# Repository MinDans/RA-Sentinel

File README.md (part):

# Project RA-Sentinel - a Radio Access Sentinel
FPGA-based Radio Receiver for securing Wifi an other access points against hacking attacks.

RA-Sentinel is an open-source project focused on creating a cost-effective, small, and low-power wide band radio receiver device that employs an FPGA to automatically detect malicious attacks on Wifi access points, such as Man in the Middle and Denial of Service attacks. By monitoring any Wifi cell, the device enhances internet safety for everyday users.
The device features low-cost receive-only chips that digitize 40 MHz of the Wifi radio spectrum at 2.4 GHz. An FPGA extracts relevant properties from demodulated and decoded packets in real-time without storage. These properties are then processed by a neural network, also implemented on the FPGA, to determine if the traffic is genuine or an attack.

 <br>
This project was funded through the NGI0 Entrust Fund, a fund established by NLnet with financial support from the European Commission's Next Generation Internet programme, under the aegis of DG Communications Networks, Content and Technology under grant agreement No 101069594.

## Latest Updates [15. Dec. 2025]

Added new firmware für the STM32 microcontroller ECU (Embedded Control Unit) on the Backend Board in "/RASBB/Software/RASBB_ECU".
It adds support for UPNP device discovery over Ethernet and provides a system configuration web page.

## System architecture

## The hardware

The hardware is a wide band SDR receiver that receives at least one complete WiFi Channel on the 2.4GHz ISM band with high resolution (12 Bits) to be able to detect smallest anomalies in a transmitted signal. The initial evaluation hardware consists of a Downcoverter/Tranceiver Chip for 2.4GHz which is widelay used in older WIFi Acess Points (MAX2831). This is followed by a 12 Bit ADC (Texas Instruments ADC3222) which converts a 40MHz window of the 2.4GHZ radio spectrum into a 4 x 240 Bit/s LVDS streams (960kBit/s total) into a XILNIX/AMD Artix7 FPGA sitting on a evaluation board made by QMTECH. 

<sub>Picture 1: First RA-Sentinel prototype based on the QM-Tech Artix7 board and a new designed RF front end connected via PMOD connector.</sub>

Based on the experience collected with with first prototype, we designed a new SDR prototypr. Two boards of the RASBB and the RASRF2400 have arrived on 23th. Feb. 2025
Testing and bringing up is now ongoing. First results and findings can be found in the corresponding Findings_Rev*.md documents.

<sub>Picture 2: RA-Sentinel prototype Revision A with RF front end board RASRF2400WB.</sub>

### Design files

**/RFFE2400WB** in this folder of this repository you find the PCB design files in KiCAD format and gerbers for the 2.4GHz 2x PMOD connected RF frontend evaluation/test board.

Link to the FPGA dev. board
[https://de.aliexpress.com/item/1005006473783593.html]

## Software / Firmware

The vast majority of the code will be written in Verilog and run on the FPGA. There is also now a firmware for the RASBB_ECU (Embedded Control Unit) and a"house keeping unit" microcontroller (STM32C031) which programms and controlling the frontend chips. The RASBB_ECI provides the interconnctivity with other systems (alarm forwarding) and the web configuration interface. This firmware is written in C. 

The firmware for the RASBB_ECU can be found <a href="https://github.com/Tobias-DG3YEV/RA-Sentinel/tree/main/RASBB/Software/RASBB_ECU">here</a>. 

The RASBB_ECU Firmware for the onboard STM32 provides a versatile configuration interface with GUI that allows to show statistics and maybe UDP for analytic packets transfer and secure TCP/IP configuration over Ethernet.
To access this, enter the IP of the RAS into your local browser like http://192.168.0.2:4842/. The IP can be easily found via network environment because the RAS supports UPNP over ethernet.

A suspected WiFi node can be

* Tracked: Monitored by relative signal strength and later with additional direction. These values are forwarded to an IDS host that can combine this information with additional data retrieved from different RAS or other network monitoring systems.
* Tagged: Marked for internal memory, moving up in watch list.
* Fingerprinted: Raw IQ data of the frame start is forwarded to a fingerprinting algorythm.

**UPNP support**

To ease the installation process, the RAS can be connected to any ethernet based LAN that provides an IPv4 DHCP server. Through the UPNP support, the RAS is easy to find in any network browser of Windows, Linux and Mac etc. 

---
## Sub project: RASRF2400WBMC - Directional RF Front End

The **RASRF2400WBMC** is a 4-channel, phase-coherent 2.4 GHz RF front-end board that extends RA-Sentinel with **Angle of Arrival (AoA)** estimation. By receiving the same signal across four spatially separated antennas, the system can estimate the physical direction of a detected attack - enabling threat localization for jamming, spoofing and unauthorized events.

This board connects to the existing RASBB via the PCIe connector and requires no hardware changes to the base band board.

> This sub-project was funded by NLnet: https://nlnet.nl/project/RA-Sentinel-directional/

See [RASRF2400WBMC/README.md](RASRF2400WBMC/README.md) for full details.

---

### Sub Projects / Project steps

The first step on this project was to have a reliable hardware basis. Initially I planned to have at least 40 Megasamples and with this 20 MHz bandwidth which is sufficient to capture the headers and the most common bandwitdhs used on 2.4GHz WiFi (802.11a,b,g) communications channel. But because 802.11n also defines the possibility to use 40MHz bandwith, I wanted the possibility to cover the complete possible channel bandwidth. This has been achieved with the first prototype hardware and prooved with the sub-project RASM2400, Radio Access Spectrum Monitor for 2400MHz. You can find all project details below.

## Sub project #1: RASM2400 - a spectrum monitor

RASM2400 stands for Radio Access Spectrum Monitor operationg on 2400MHZ. It offers a visual spectrum analyzer design that runs on the evaluation hardware set of RA-Sentinel the Artix7 XC7A100T Wukong board and the RFFE2400 front end board.
It shall proove that a 40MHz wide radio spectrum can be received and transported into the FPGA. Further, this project may already be useable for first RF forensics. Feel free to download all the stuff and build an RASM by yourself.

The following diagram shows the system architecture of the RASM2400.

The output of the HDMI port of the QMTECH Wukong board.

Watch a short demonstration on Youtube by clicking on the thumbnail below.

### Software

In this repository you'll find also all software paerts needed to get the project up and running.

**/RASM2400_Verilog**

This folder contains the Verilog source files as well as a ready to program bit stream file. 

**/RASM2400_HKU**

Here you find the firmware for the RF board housekeeping unit. It does not do much a the moment but initializing the Downconverter MAX2831 and the ADC3222. It is planned to receive commands via I2C to change basic parameters wil center frequency, sensitivity and AGC characteristics. This porject can be compiled with arm-gcc or with the free available and Eclipse based development environment (IDE) from ST called "STM32CubeIDE". You can download this IDE from ST.com [https://www.st.com/en/development-tools/stm32cubeide.html]

### Project update 13th Oct. 2024

The target of the next Milestone #2 was the „Identification and isolation of appropriate software components“ and also to „Additionally apply modifications to the openOFDM module to get extra meta data out of the frame demodulator to have a wider data basis for the later fingerprinting process.“

In the following points I describe how I achieved each step of this Milestone.

**1. compile/synthesize openWiFi on the target FPGA**

The code of openWiFi has been successfully ported from the project GitHub site [1] to the evaluation setup that I have designed and set up in the first Milestone. After gluing together the ADC LVDS deserializer block inside the FPGA with the parallel input of the openOFDM core, got rid of several timing constraint issues, I finally achieved to decode a WiFi Frame coming from an arbitrary signal generator. To accomplish this target, the code needed to be isolated from the original open WiFi demo project code. This original demo was based on SDR evaluation boards relying all on the AMD ZYNQ FPGA-ARM chip family. This family provides an FPGA part and an integrated ARM micro processor to which all communication of the FPGA part is connected to. Data from and to the integrated processor is exchanged through a common memory bus. This however is not working with my design idea which is based on a more powerful FPGA with an external ARM co-processor. I tried extracting the needed HDL (Verilog) parts and make this code running stand-alone. Finally I came the conclusion that only the project „openOFDM“ needs to be ported to my RA-Sentinel project hardware because the network layer and the transmit part implemented in openWiFi is not really needed by the RA-Sentinel project because there is no need in routing real data back and forth to a network. We are only interested in the lowest layer of a WiFi frame and its analog characteristics, not the routing of packets and also not in the frame containing payload as such.

First I adapted the test-bench provided in [2] for the Vivado simulation environment. To be able to simulate the complete RA-Sentinel hardware, I created a LVDS emulator that can stream artificial synthesized and recorded  RF data coming originally from the TI ADC 3221. After providing recorded RF data via this LVDS simulator and generating a appropriate, to the ADC phase-locked master clock of 100MHz to the openOFDM core and (see top_tb.v), this setup was able to decode a complete 802.11a/g frame in the AMD Vivado simulator. It took me quite some fiddling and playing with timings and implementation settings of the tool-chain to finally get it running properly on my own hardware. (AMD Artix7 development board my QM-Tech and my 2.4GHz ADC board designed in Milestone 1)

**2. Strip down openWiFi and open OFDM to the receive part**

First this was regarded as an easy task but as deeper I dived into the code  by the original author of the two projects, the more I realized the code provides almost no comments and wire and register definitions are quite ambiguous and non-intuitive. In my opinion the code needed desperately a rework to be better understandable which would also lead to a lower learning curve for others also trying to implement and adapt the existing code base to their needs. Two major things I tried improving with my fork of openOFDM: The introduction of directional prefixes for module ports. I have seen such in the code of another NLnet founded guy called Dan Nissselquist. Adding the prefix  „i_“ to  input ports (defined as wires/registers in Verilog) and „o_“ to the port definition makes it IMHO much easier when browsing through the code, allowing to instantly realize which wire or register is being exported from this current module and which is only a local element. I added these prefixes all over the code of openOFDM. See my fork of openOFDM on GitHub [1] for details. The next thing I found hard to understand, was the use of the ever repeating word „sample“ for all data along the signal path, from the input of the openOFDM core (ADC base-band data) up to near the exit (decoded data bytes). As there is a switch from time domain (endless sample stream) into frequency domain (blocks of 64 frequency bands) in the module „sync_long“, I changed the name of all wires and registers after this module and renamed them into „spectrum“.  Also some comments were added to clarify what a wire or register is doing at a certain point. This work is not yet regarded as being completed. Each time I dig into the original code, I will add comments and try to make the code more „barrier free“.

**3. Create a new fork of openOFDM**

This has been done and the new fork of openOFDm can be found here:

[1] https://github.com/Tobias-DG3YEV/openofdm

It contains comments and my code changes proposed earlier in this document.

**4. Try adding additional meta date stubs**

As I tried figuring out which meta data could be used to distinguish between  genuine transmitting device and a counterfeit device, I found an article at mathworks.com [3] reporting that they proved finding counterfeit, evil twins of a WiFi Access Point by feeding the raw sampled channel data of a transmission into a ML algorithm. For this purpose they followed a kind of a brute force approach by taking all samples of a received frame into account and fed into a ML algorithm. Even the smallest frame like an information or flow control frame that is only 100uS of duration will produce 16kBytes of data which is rather huge. This amount of data may be processable - if the SDR is directly connected to a powerful computer with multiple cores etc. The project RA-Sentinel does not follow this kind of big processing power approach. Amplitude, phase and frequency change due to several effects during the transmission of a frame, but all of these changes always result in a phase shift. So I thought, in  the first attempt identifying a WiFi transmitting device by characterizing (or say learning) the phase deviation over time may be sufficient. Because the RF receiver front end of the RA-Sentinel project has a low noise and high stability master clock (a 40MHz TXCO by Abracom) that is multiple times more accurate that standard commercial WiFi transmitters, I hope that a small amount of phase shift data received in the beginning of a WiFi frame may be enough to clearly identify counterfeit devices. 

**5. Redefine a new simplified interface to access meta parameters**

One thing I have learned throughout the project progress so far, is that even many may say that an FPGA is one of the most versatile digital programmable devices available today, allowing the implementation of any kind of parallel and sequential tasks up to integration of soft-core processors the fact is that all this integrated logic leads to a rather time consuming iterative development process. To optimize WiFi data reception on one side and to interpret and forward meta data on the other side all inside the FPGA leads to an extremely slow and challenging development process. For the analysis of meta data, an external, traditional single chip microprocessor running straight C/C++ code,  offers much more opportunities and most importantly, allows much a faster  development progress. Bit for that, I need a fast and reliable interconnection between the FPGA and the micro processor.

I identified and implemented two interfaces which allow to access 

The first interface I implemented into the FPGA was the SPI slave interface. This interface allows reading and writing 32 wide registers inside the FPGA by an external micro controller (in this case, I use a STM32H743 Cortex-M7)

The SPI interface allows access to the following parameters:

- Receiver characteristics like receiver center frequency, gain, power threshold, max. error rate etc.

- reading current receiver parameters like noise level, signal to noise ratio etc.

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
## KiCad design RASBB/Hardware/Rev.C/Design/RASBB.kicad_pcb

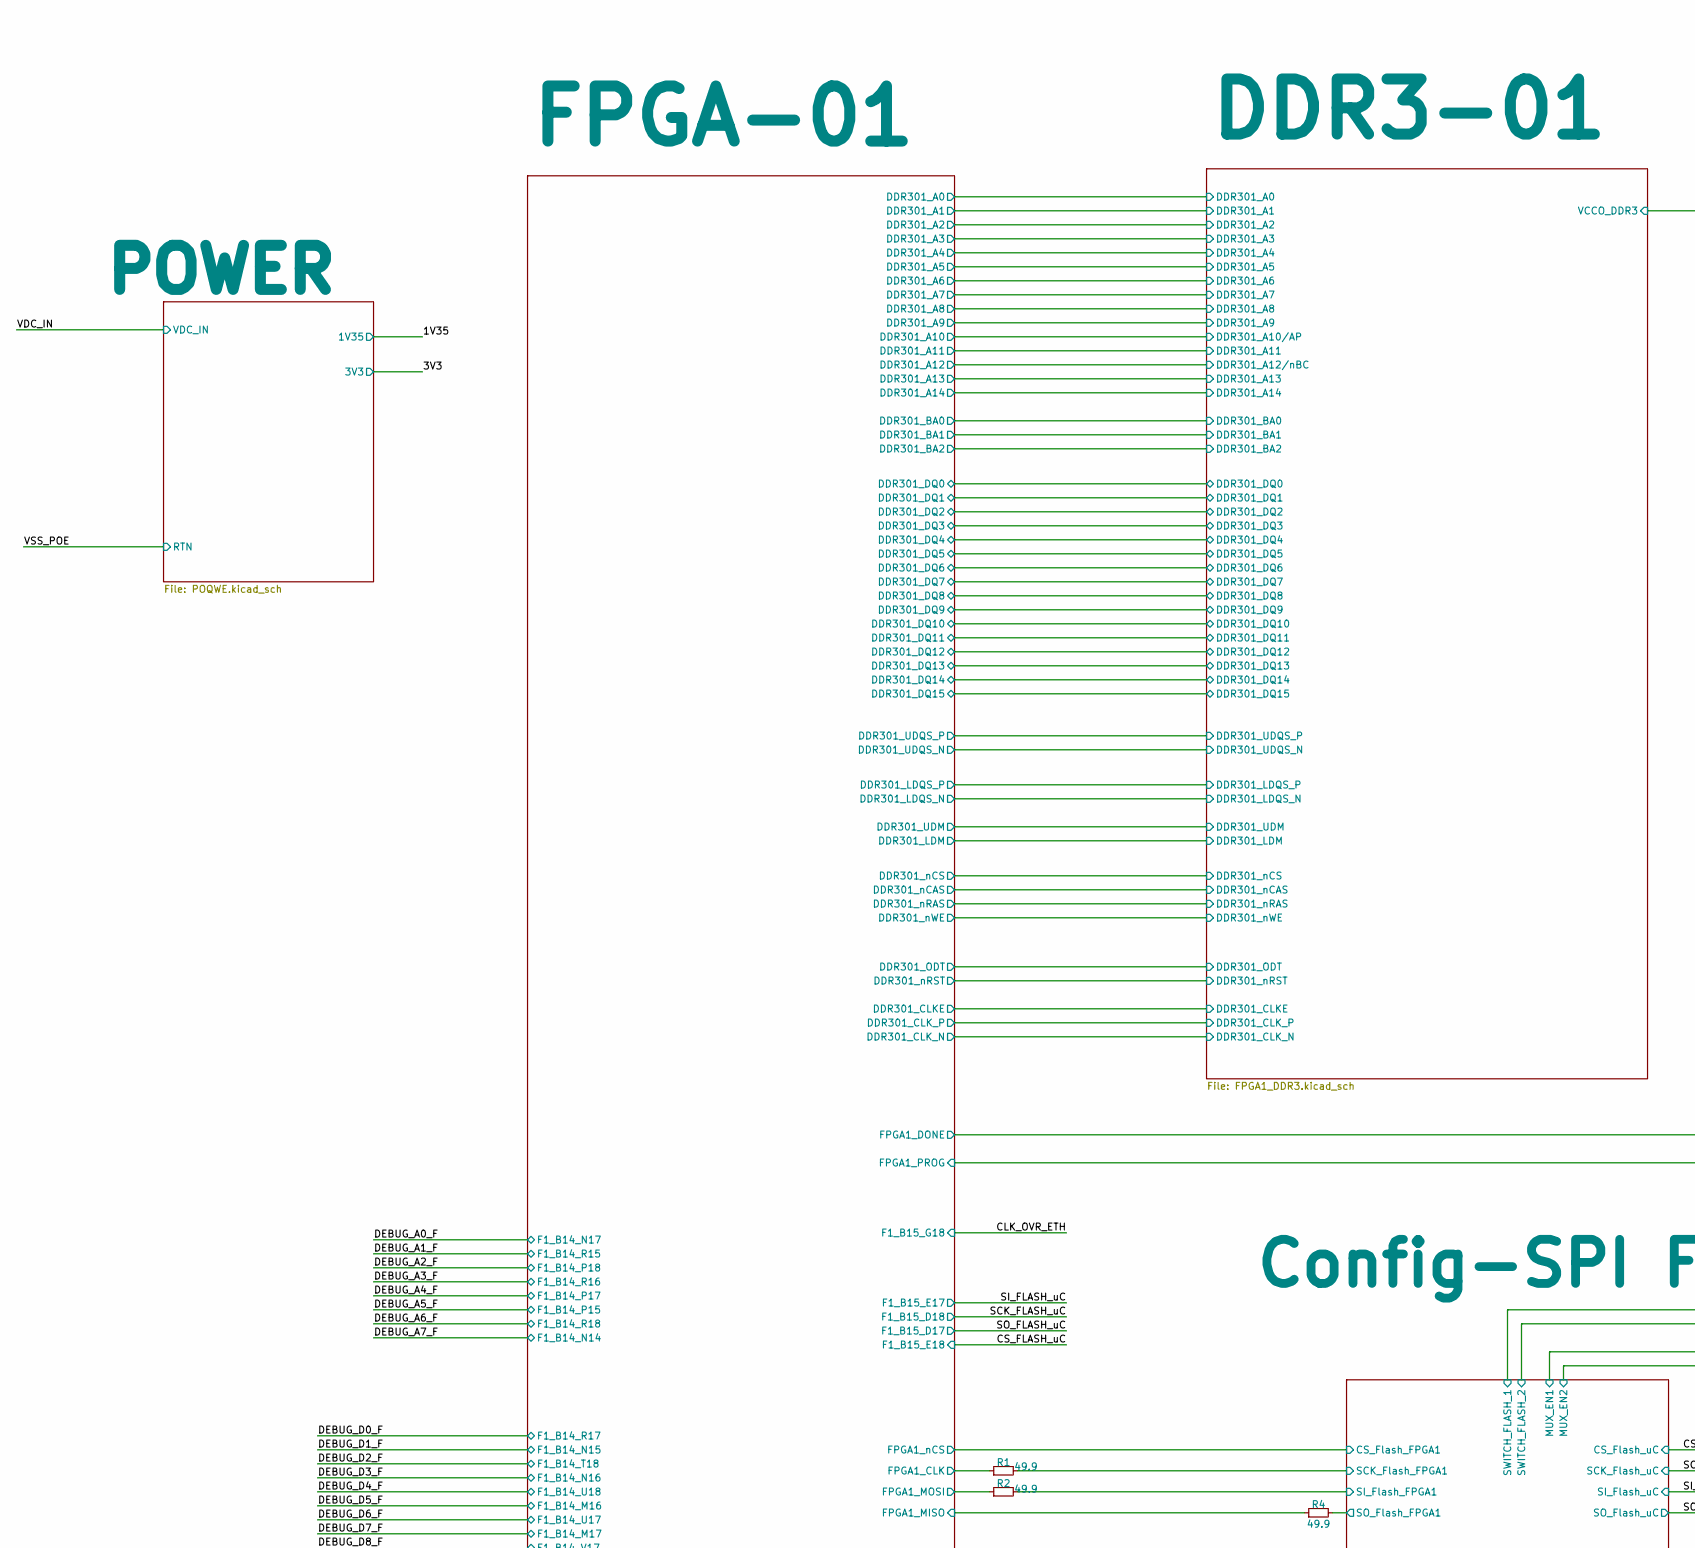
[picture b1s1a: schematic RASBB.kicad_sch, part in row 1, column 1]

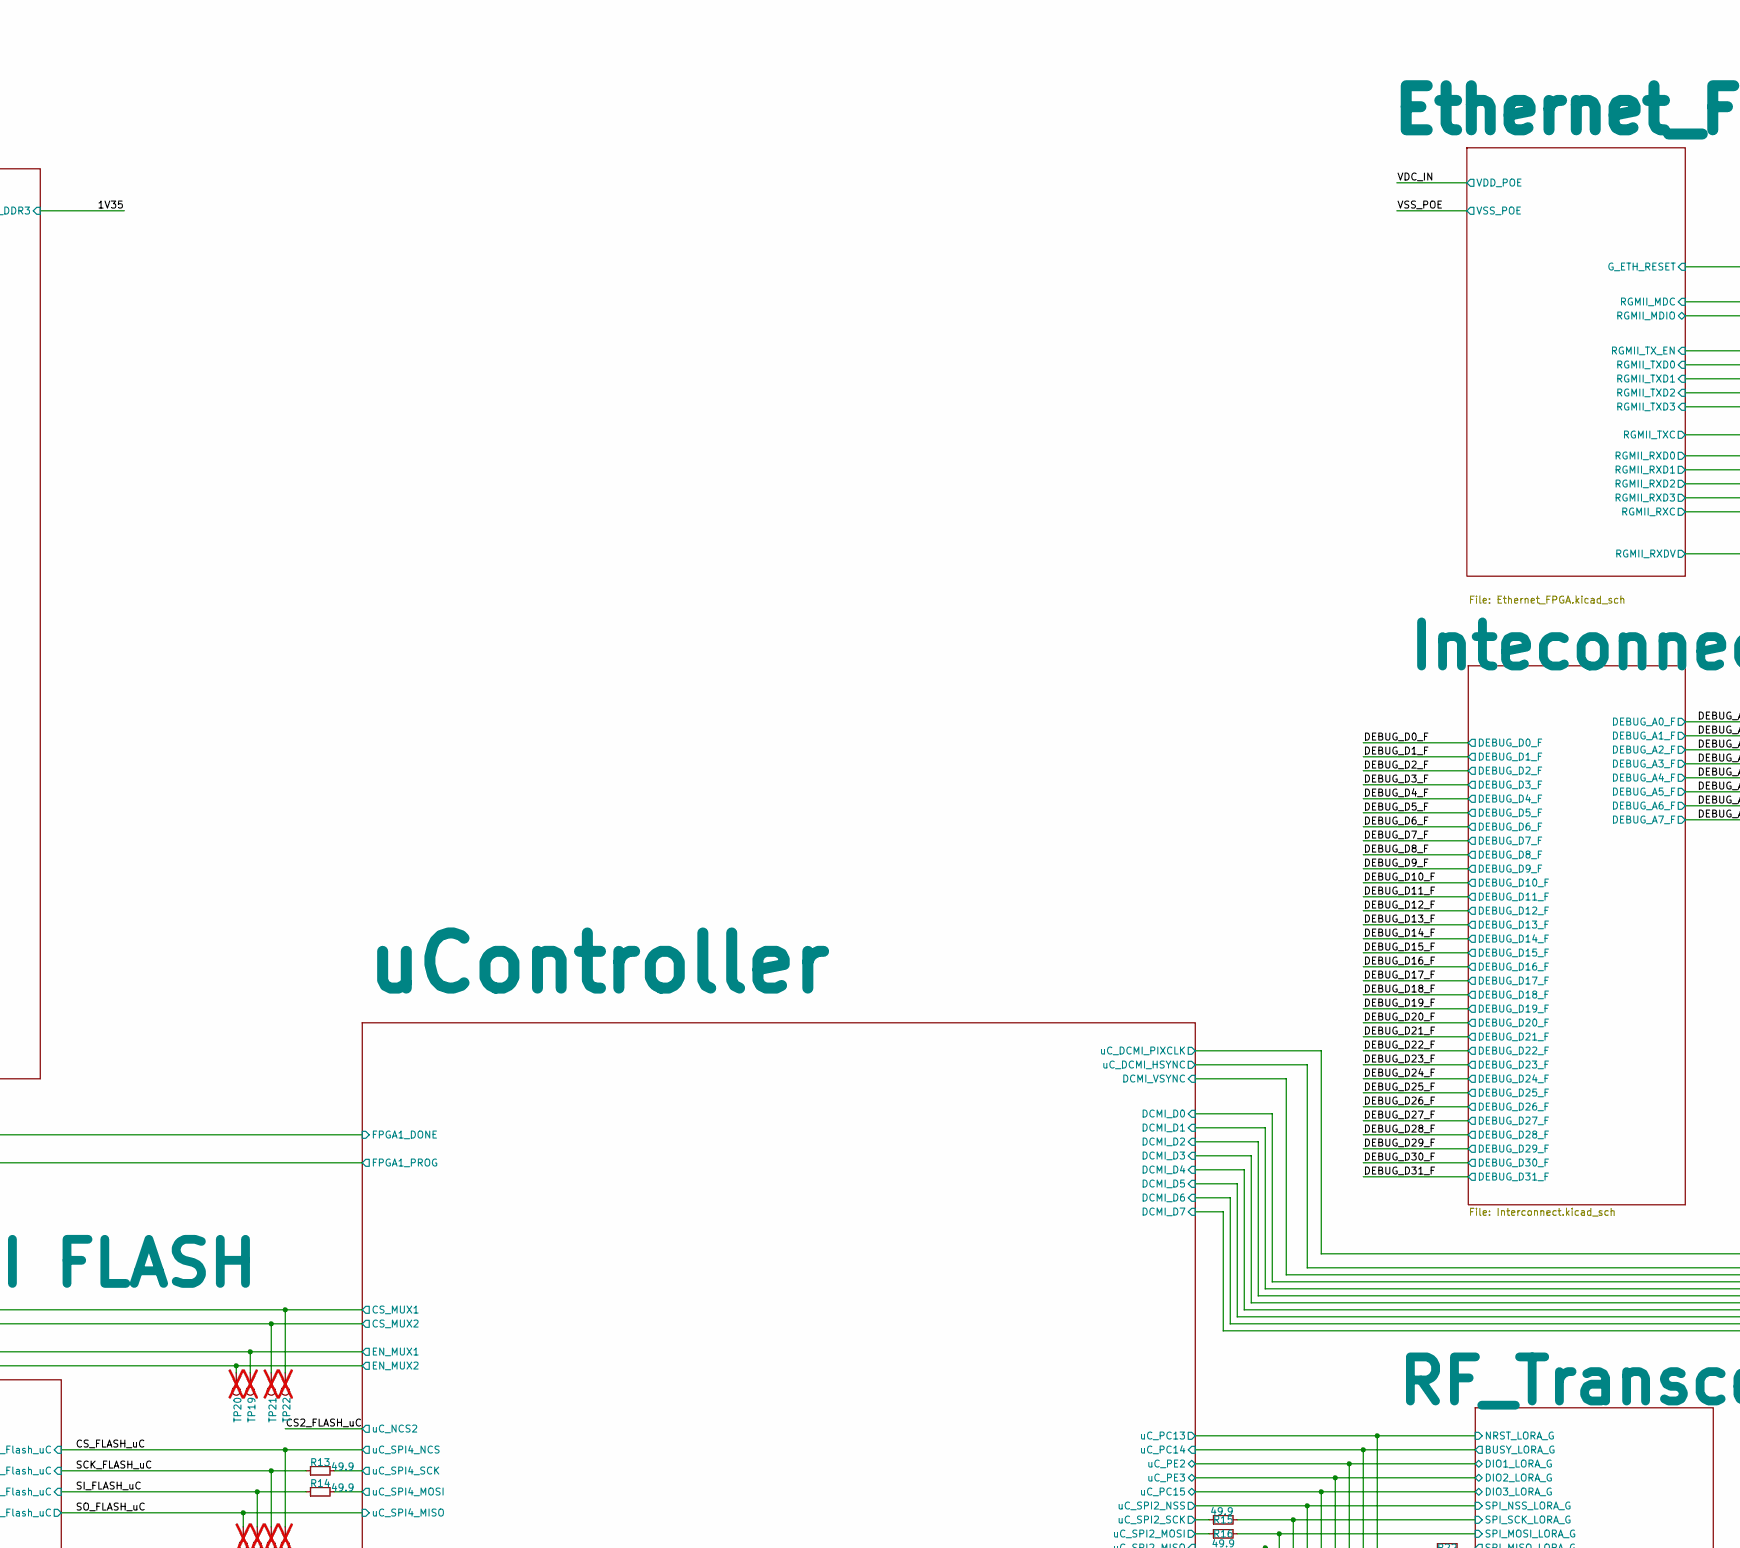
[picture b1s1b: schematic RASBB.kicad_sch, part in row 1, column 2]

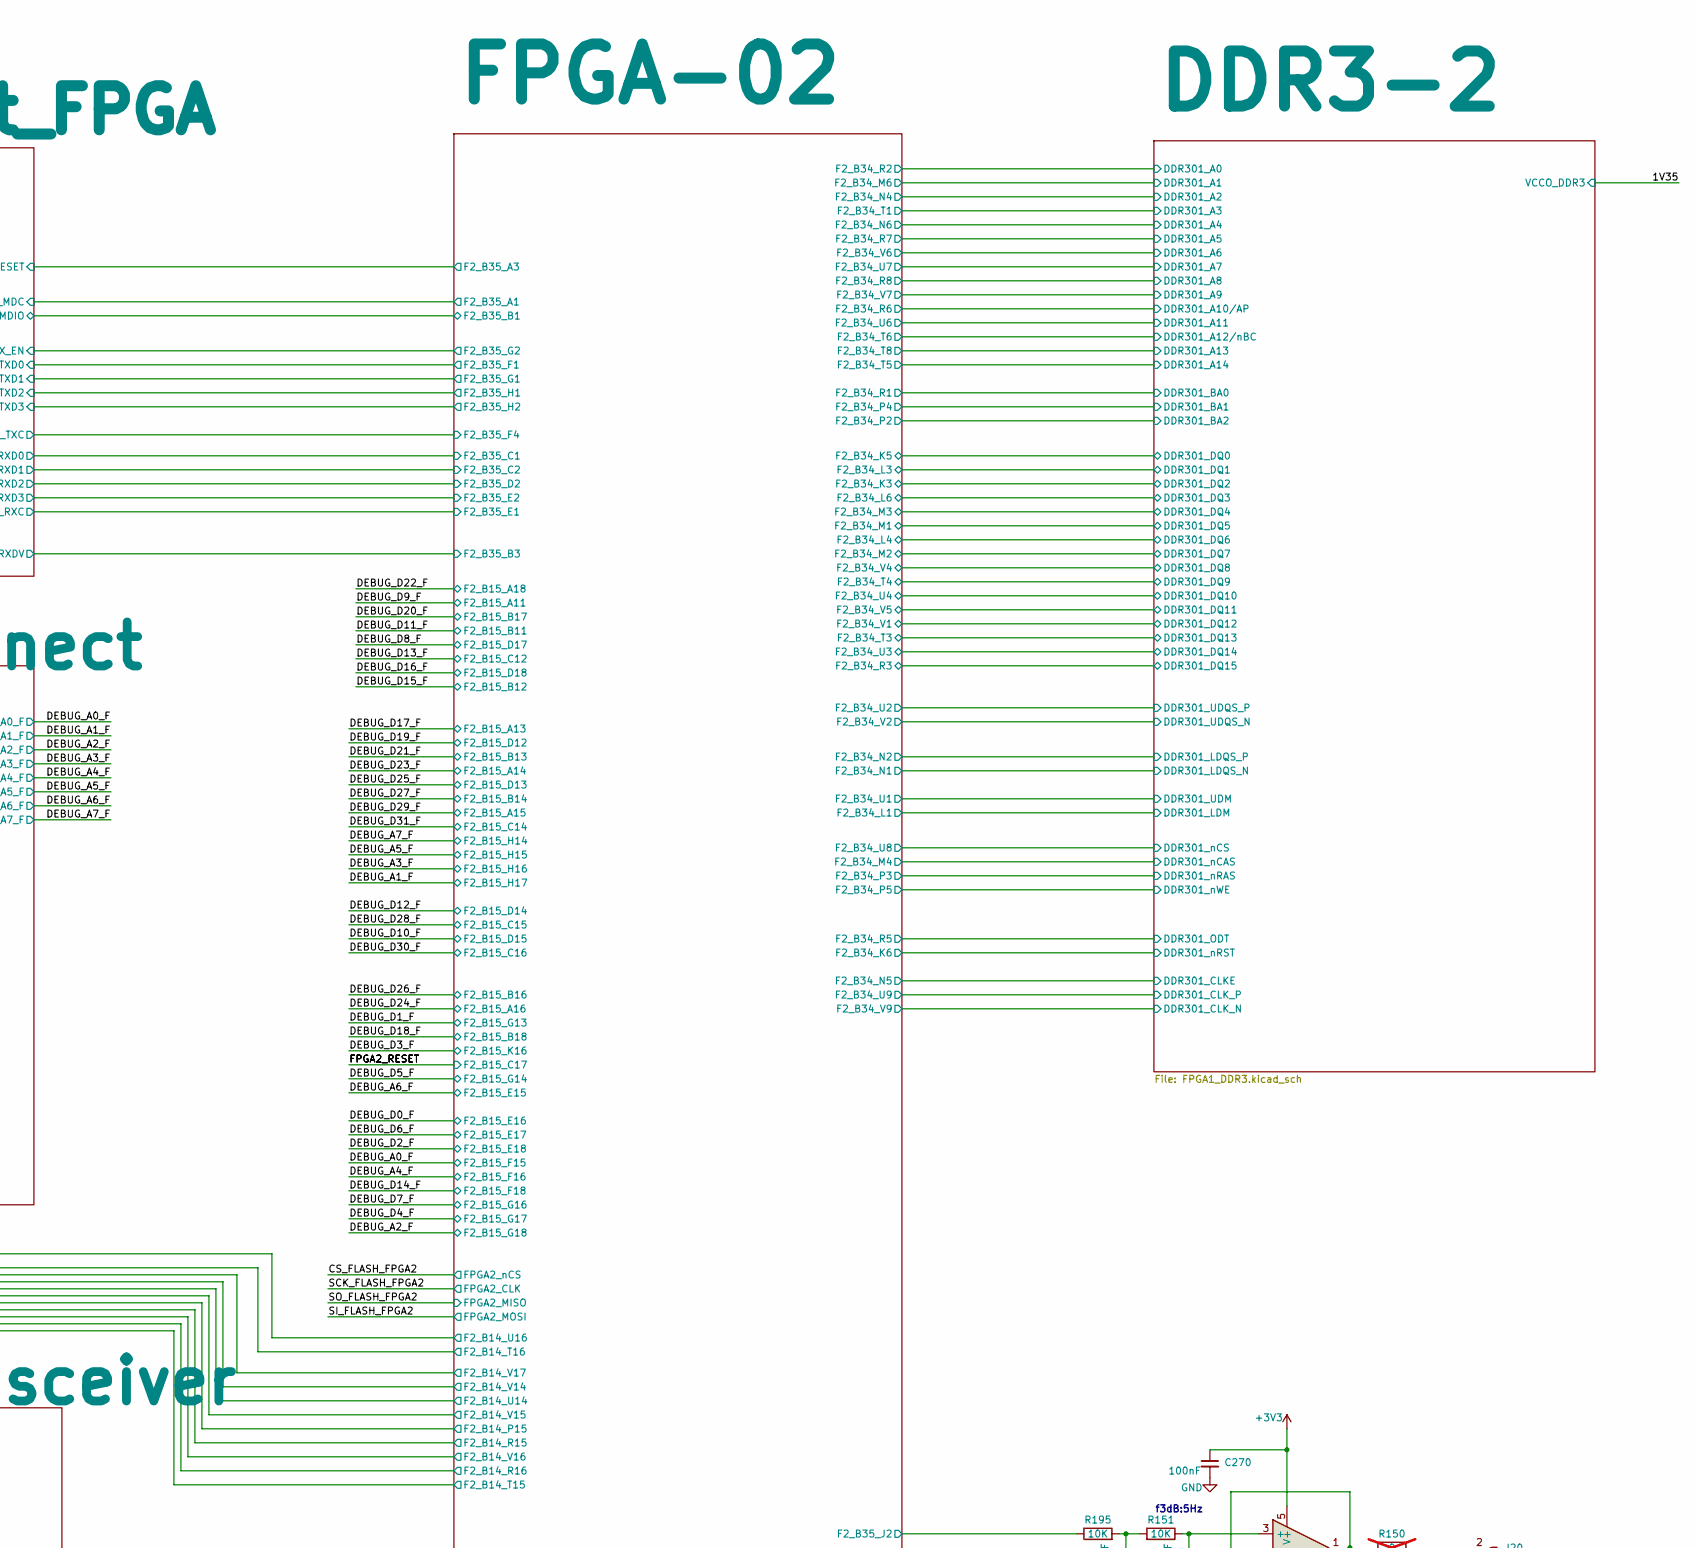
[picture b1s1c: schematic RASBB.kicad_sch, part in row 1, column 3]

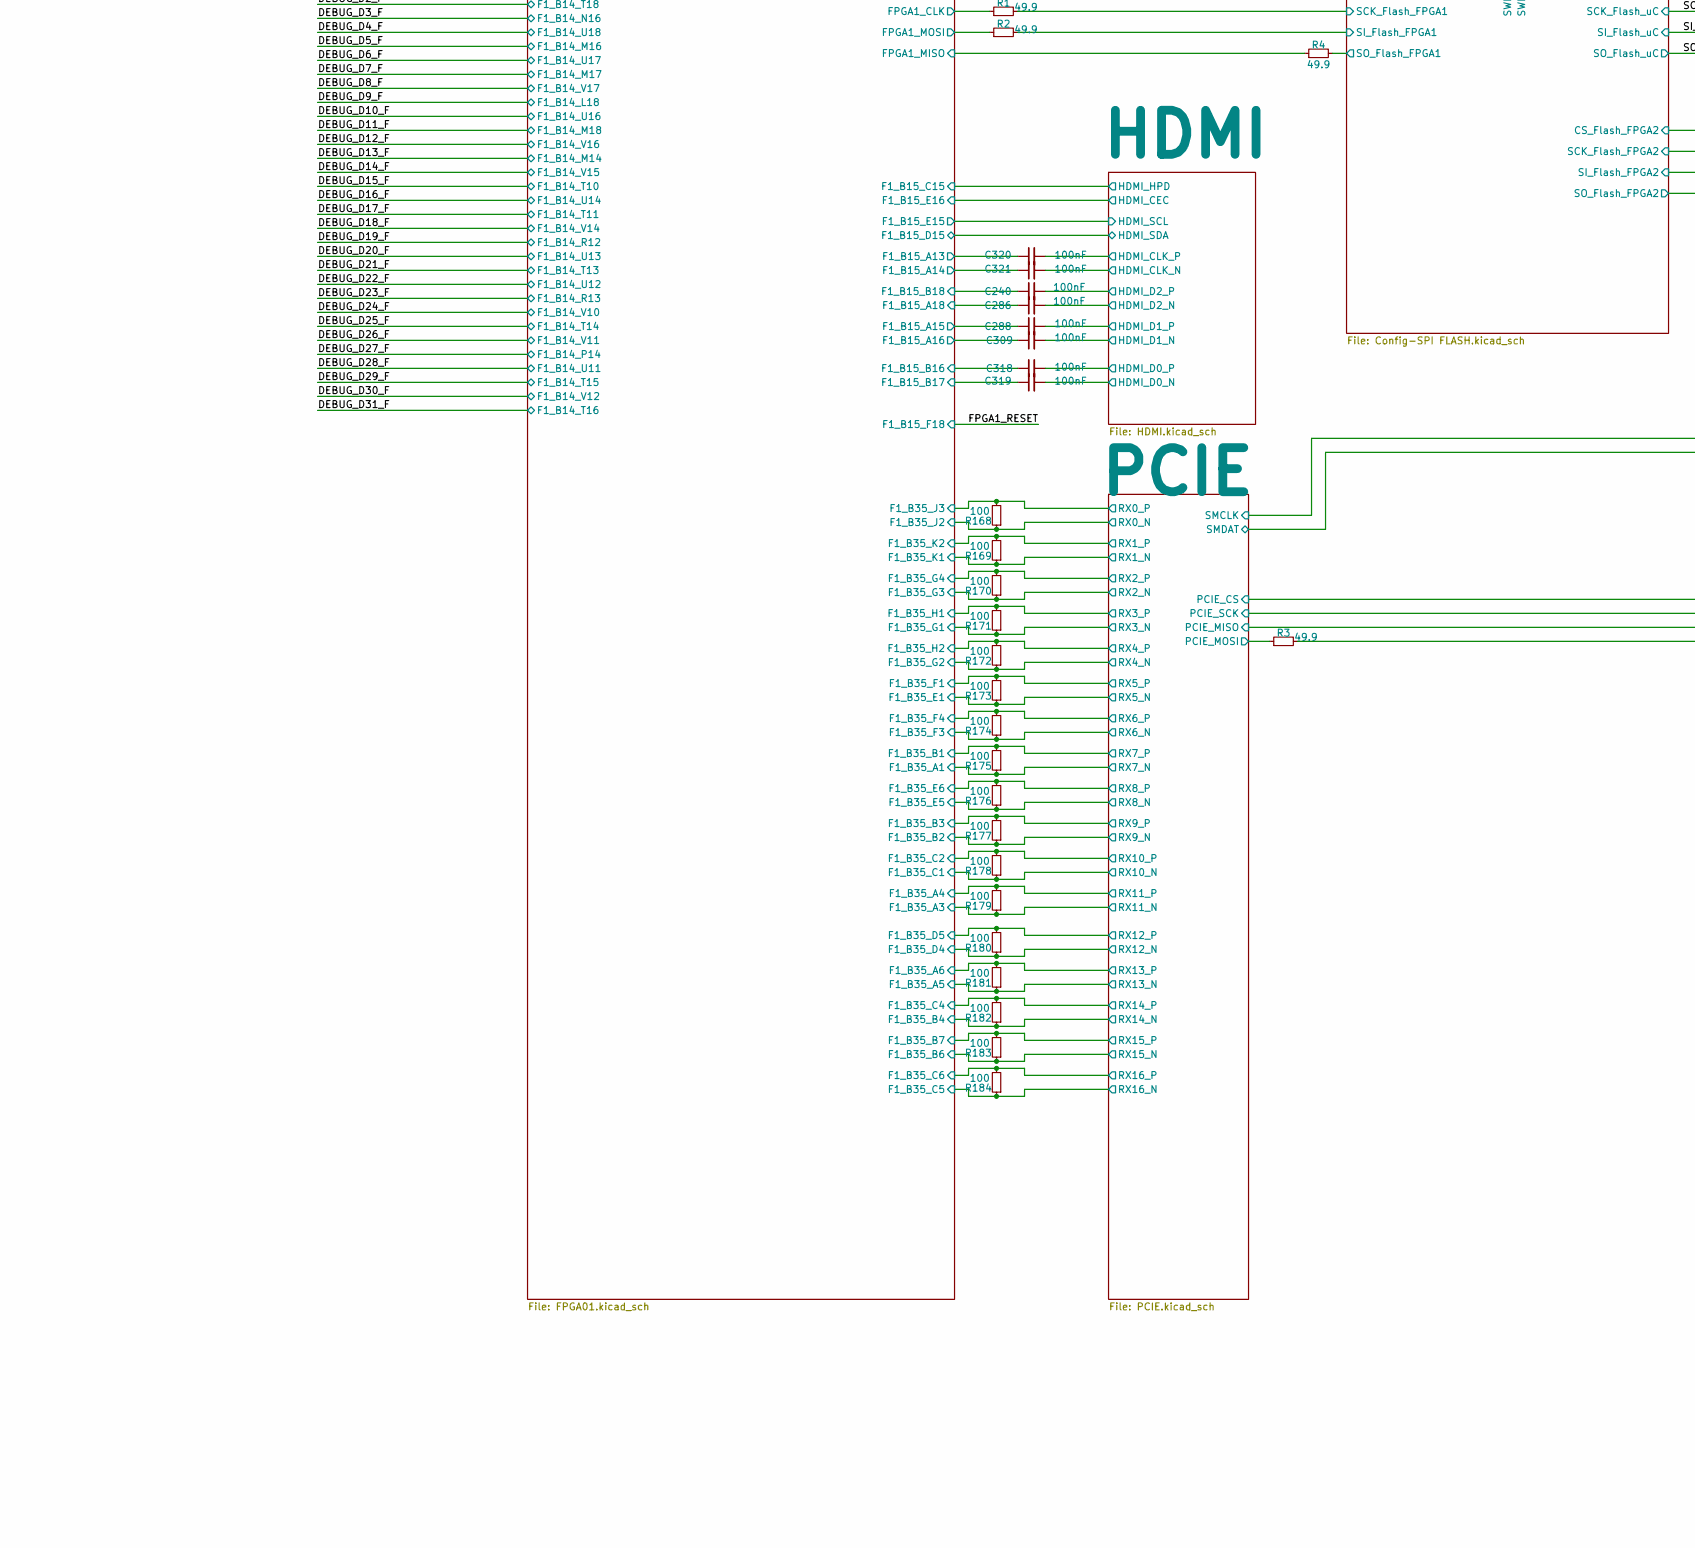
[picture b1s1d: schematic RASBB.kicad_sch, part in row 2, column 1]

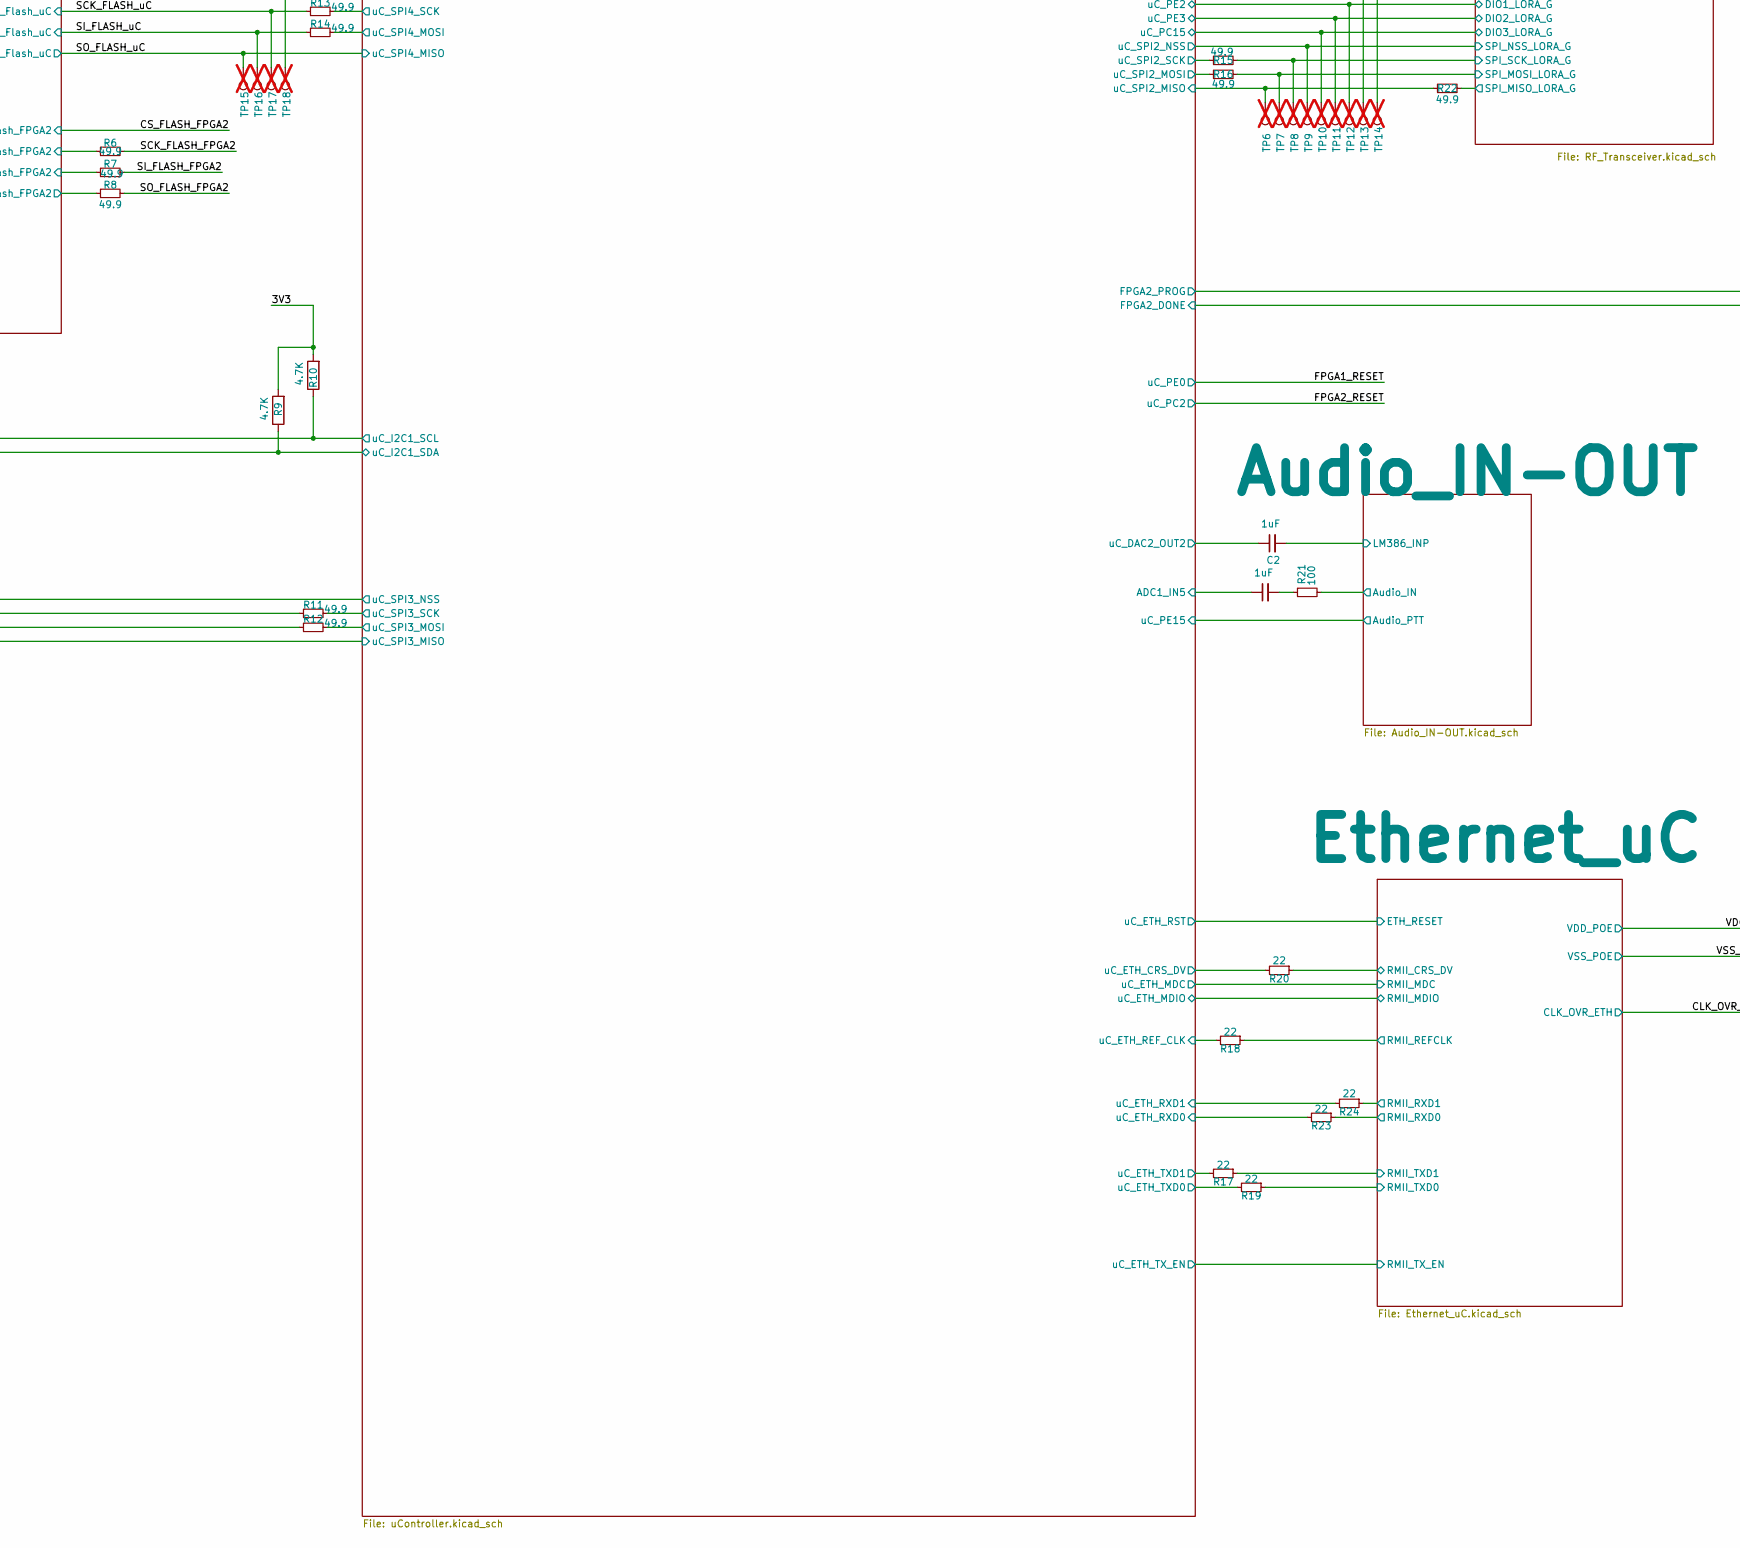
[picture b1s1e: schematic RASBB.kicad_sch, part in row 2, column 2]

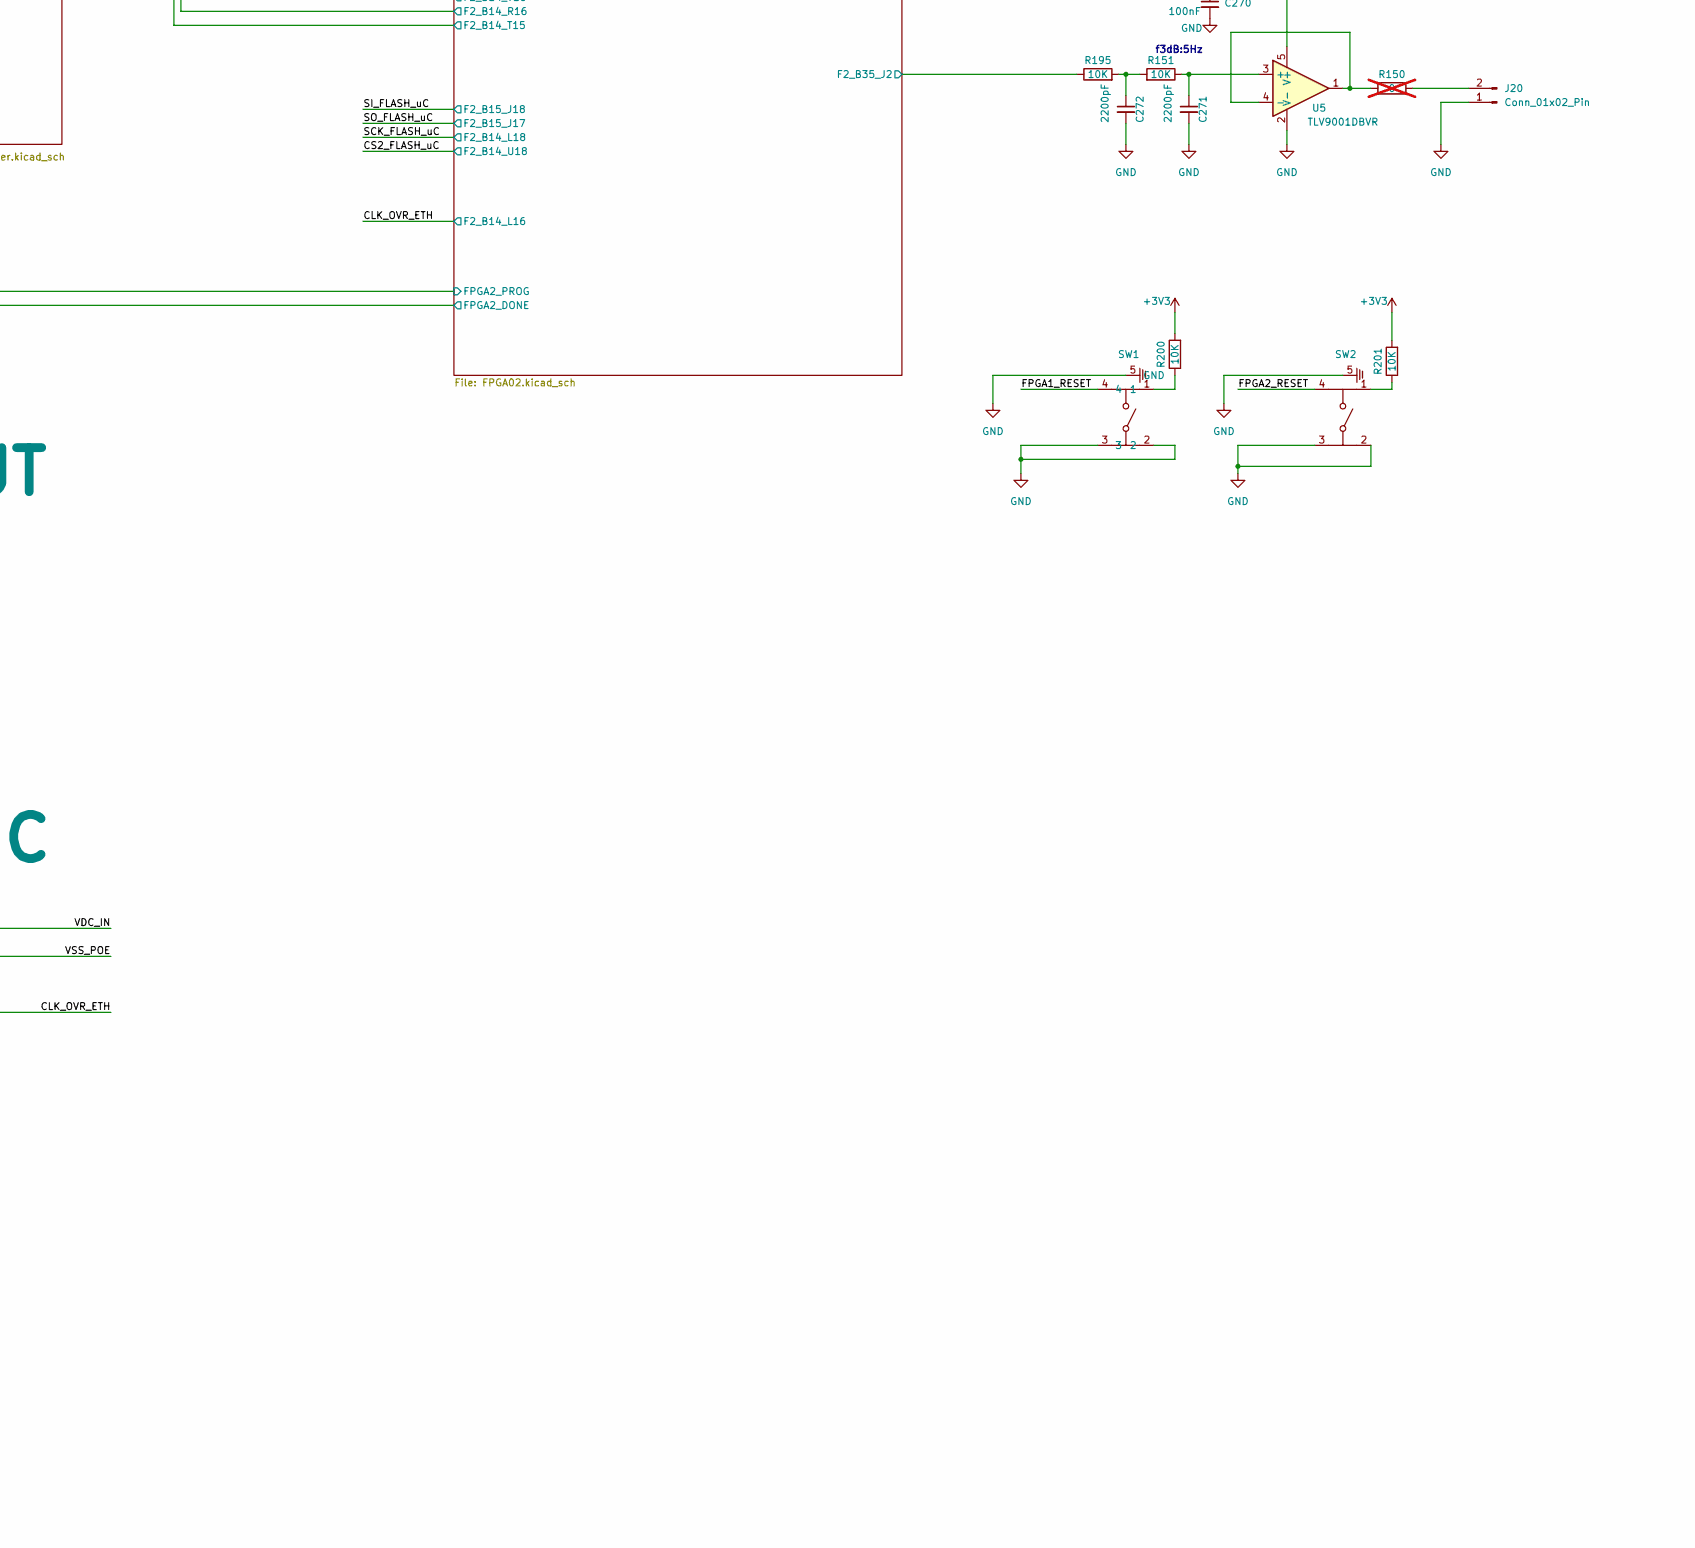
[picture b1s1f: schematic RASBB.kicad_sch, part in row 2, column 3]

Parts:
C1, C2: 1uF; C_0402_1005Metric; Mfr. Part # 0402X105M160CT; LCSC Part # C3889771
C240, C286, C288, C309, C318, C319, C320, C321: 100nF; C_0402_1005Metric; Mfr. Part # 0402B104K500CT; LCSC Part # C152814
C270: 100nF; C_0402_1005Metric; Manufacturer_Part_Number GRM155R71A104KA01D; LCSC Part # C152814
C271: 2200pF; C_0402_1005Metric; Manufacturer_Part_Number GRM1555C1H222JA01D
C272: 2200pF; C_0402_1005Metric; Manufacturer_Part_Number GRM1555C1H222JA01D; LCSC Part # C1531
J20: Conn_01x02_Pin; PinHeader_1x02_P2.54mm_Vertical; Mfr. Part # PZ254V-11-02P; LCSC Part # C492401
R1, R2, R3, R4, R6, R7, R8, R11, R12, R13, R14, R15, R16, R22: 49.9; R_0402_1005Metric; Mfr. Part # RMCF0402FT49R9; LCSC Part # C4229190
R9, R10: 4.7K; R_0402_1005Metric; Mfr. Part # WR04X4701FTL; LCSC Part # C163826
R17, R18, R19, R20, R23, R24: 22; R_0402_1005Metric; Mfr. Part # WR04X22R0FTL; LCSC Part # C163821
R21: 100; R_0402_1005Metric; Mfr. Part # WR04X1000FTL; LCSC Part # C163808
R150: 0; R_0603_1608Metric; Manufacturer_Part_Number RC0603JR-070RL; not fitted
R151: 10K; R_0603_1608Metric; Manufacturer_Part_Number RC0603FR-0710KL
R168, R169, R170, R171, R172, R173, R174, R175, R176, R177, R178, R179, R180, R181, R182, R183, R184: 100; R_0402_1005Metric; Mfr. Part # WR02X1000FTL; LCSC Part # C367410
R195, R200, R201: 10K; R_0603_1608Metric; Manufacturer_Part_Number RC0603FR-0710KL; LCSC Part # C25804
SW1, SW2: 435451019820; Part Number 435451019820
TP6, TP7, TP8, TP9, TP10, TP11, TP12, TP13, TP14, TP15, TP16, TP17, TP18, TP19, TP20, TP21, TP22: TestPoint; TestPoint_Pad_D1.0mm; not fitted
U5: TLV9001DBVR; SOT-23-5; Manufacturer_Part_Number TLV9001DBVR

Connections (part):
+3V3: C270.1, R9.2, R10.2, R200.2, R201.2, U5.5 (V+); also elsewhere on the board
/Audio_IN-OUT/Audio_IN: R21.2; also elsewhere on the board
/Audio_IN-OUT/LM386_INP: C2.2; also elsewhere on the board
/CS_FLASH_uC: TP18.1 (1_1); also elsewhere on the board
/Config-SPI FLASH/MUX_EN1: TP19.1 (1_1); also elsewhere on the board
/Config-SPI FLASH/MUX_EN2: TP20.1 (1_1); also elsewhere on the board
/Config-SPI FLASH/SCK_Flash_FPGA1: R1.2; also elsewhere on the board
/Config-SPI FLASH/SCK_Flash_FPGA2: R6.1; also elsewhere on the board
/Config-SPI FLASH/SI_Flash_FPGA1: R2.2; also elsewhere on the board
/Config-SPI FLASH/SI_Flash_FPGA2: R7.1; also elsewhere on the board
/Config-SPI FLASH/SO_Flash_FPGA1: R4.2; also elsewhere on the board
/Config-SPI FLASH/SO_Flash_FPGA2: R8.1; also elsewhere on the board
/Config-SPI FLASH/SWITCH_FLASH_1: TP22.1 (1_1); also elsewhere on the board
/Config-SPI FLASH/SWITCH_FLASH_2: TP21.1 (1_1); also elsewhere on the board
/Ethernet_uC/RMII_CRS_DV: R20.1; also elsewhere on the board
/Ethernet_uC/RMII_REFCLK: R18.1; also elsewhere on the board
/Ethernet_uC/RMII_RXD0: R23.1; also elsewhere on the board
/Ethernet_uC/RMII_RXD1: R24.1; also elsewhere on the board
/Ethernet_uC/RMII_TXD0: R19.1; also elsewhere on the board
/Ethernet_uC/RMII_TXD1: R17.1; also elsewhere on the board
/FPGA1_RESET: SW1.4; also elsewhere on the board
/FPGA2_RESET: SW2.4; also elsewhere on the board
/FPGA-01/F1_B15_A13: C320.1; also elsewhere on the board
/FPGA-01/F1_B15_A14: C321.1; also elsewhere on the board
/FPGA-01/F1_B15_A15: C288.1; also elsewhere on the board
/FPGA-01/F1_B15_A16: C309.1; also elsewhere on the board
/FPGA-01/F1_B15_A18: C286.1; also elsewhere on the board
/FPGA-01/F1_B15_B16: C318.1; also elsewhere on the board
/FPGA-01/F1_B15_B17: C319.1; also elsewhere on the board
/FPGA-01/F1_B15_B18: C240.1; also elsewhere on the board
/FPGA-01/FPGA1_CLK: R1.1; also elsewhere on the board
/FPGA-01/FPGA1_MISO: R4.1; also elsewhere on the board
/FPGA-01/FPGA1_MOSI: R2.1; also elsewhere on the board
/FPGA-02/F2_B35_J2: R195.1; also elsewhere on the board
/HDMI/HDMI_CLK_N: C321.2; also elsewhere on the board
/HDMI/HDMI_CLK_P: C320.2; also elsewhere on the board
/HDMI/HDMI_D0_N: C319.2; also elsewhere on the board
/HDMI/HDMI_D0_P: C318.2; also elsewhere on the board
/HDMI/HDMI_D1_N: C309.2; also elsewhere on the board
/HDMI/HDMI_D1_P: C288.2; also elsewhere on the board
/HDMI/HDMI_D2_N: C286.2; also elsewhere on the board
/HDMI/HDMI_D2_P: C240.2; also elsewhere on the board
/PCIE/PCIE_MISO: R12.1; also elsewhere on the board
/PCIE/PCIE_MOSI: R3.1; also elsewhere on the board
/PCIE/PCIE_SCK: R11.1; also elsewhere on the board
/PCIE/RX0_N: R168.1; also elsewhere on the board
/PCIE/RX0_P: R168.2; also elsewhere on the board
/PCIE/RX1_N: R169.1; also elsewhere on the board
/PCIE/RX1_P: R169.2; also elsewhere on the board
/PCIE/RX2_N: R170.1; also elsewhere on the board
/PCIE/RX2_P: R170.2; also elsewhere on the board
/PCIE/RX3_N: R171.1; also elsewhere on the board
/PCIE/RX3_P: R171.2; also elsewhere on the board
/PCIE/RX4_N: R172.1; also elsewhere on the board
/PCIE/RX4_P: R172.2; also elsewhere on the board
/PCIE/RX5_N: R173.1; also elsewhere on the board
/PCIE/RX5_P: R173.2; also elsewhere on the board
/PCIE/RX6_N: R174.1; also elsewhere on the board
/PCIE/RX6_P: R174.2; also elsewhere on the board
/PCIE/RX7_N: R175.1; also elsewhere on the board
/PCIE/RX7_P: R175.2; also elsewhere on the board
/PCIE/RX8_N: R176.1; also elsewhere on the board
/PCIE/RX8_P: R176.2; also elsewhere on the board
/PCIE/RX9_N: R177.1; also elsewhere on the board
/PCIE/RX9_P: R177.2; also elsewhere on the board
/PCIE/RX10_N: R178.1; also elsewhere on the board
/PCIE/RX10_P: R178.2; also elsewhere on the board
/PCIE/RX11_N: R179.1; also elsewhere on the board
/PCIE/RX11_P: R179.2; also elsewhere on the board
/PCIE/RX12_N: R180.1; also elsewhere on the board
/PCIE/RX12_P: R180.2; also elsewhere on the board
/PCIE/RX13_N: R181.1; also elsewhere on the board
/PCIE/RX13_P: R181.2; also elsewhere on the board
/PCIE/RX14_N: R182.1; also elsewhere on the board
/PCIE/RX14_P: R182.2; also elsewhere on the board
/PCIE/RX15_N: R183.1; also elsewhere on the board
/PCIE/RX15_P: R183.2; also elsewhere on the board
/PCIE/RX16_N: R184.1; also elsewhere on the board
/PCIE/RX16_P: R184.2; also elsewhere on the board
/PCIE/SMCLK: R10.1; also elsewhere on the board
/PCIE/SMDAT: R9.1; also elsewhere on the board
/RF_Transceiver/BUSY_LORA_G: TP13.1 (1_1); also elsewhere on the board
/RF_Transceiver/DIO1_LORA_G: TP12.1 (1_1); also elsewhere on the board
/RF_Transceiver/DIO2_LORA_G: TP11.1 (1_1); also elsewhere on the board
/RF_Transceiver/DIO3_LORA_G: TP10.1 (1_1); also elsewhere on the board
/RF_Transceiver/NRST_LORA_G: TP14.1 (1_1); also elsewhere on the board
/RF_Transceiver/SPI_MISO_LORA_G: R22.2; also elsewhere on the board
/RF_Transceiver/SPI_MOSI_LORA_G: R16.2, TP7.1 (1_1); also elsewhere on the board
/RF_Transceiver/SPI_NSS_LORA_G: TP9.1 (1_1); also elsewhere on the board
/RF_Transceiver/SPI_SCK_LORA_G: R15.2, TP8.1 (1_1); also elsewhere on the board
/SCK_FLASH_FPGA2: R6.2; also elsewhere on the board
/SCK_FLASH_uC: R13.1, TP17.1 (1_1); also elsewhere on the board
/SI_FLASH_FPGA2: R7.2; also elsewhere on the board
/SI_FLASH_uC: R14.1, TP16.1 (1_1); also elsewhere on the board
/SO_FLASH_FPGA2: R8.2; also elsewhere on the board
/SO_FLASH_uC: TP15.1 (1_1); also elsewhere on the board
/uController/ADC1_IN5: C1.1; also elsewhere on the board
/uController/uC_DAC2_OUT2: C2.1; also elsewhere on the board
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
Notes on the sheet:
f3dB:5Hz

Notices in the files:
RASBB/Hardware/Rev.C/Design/RASBB.kicad_pcb:
Licensed under CERN-OHL-S-2.0
RASRF2400WB/Hardware/PCB_Design/ADC3221.kicad_sch:
GNU GENERAL PUBLIC LICENSE Version 2, June 1991
